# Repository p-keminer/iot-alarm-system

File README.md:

<div align="center">

</div>

---

<div align="center">
  
  &nbsp;&nbsp;&nbsp;&nbsp;&nbsp;&nbsp;
  
  &nbsp;&nbsp;&nbsp;&nbsp;&nbsp;&nbsp;
 
</div>

---

# IoT-Alarmanlage

Die IoT-Alarmanlage basiert auf einem `Elegoo Uno R3`, zwei `ESP8266` und einem `Raspberry Pi Zero 2 W`. RFID und zwei Reed-Sensoren steuern die lokale Alarm-FSM. Ein Funkpfad uebertraegt Alarmzustaende an den Empfaenger; das Dashboard zeigt Telemetrie, Logs und Aufnahmen und sendet freigegebene Befehle.

Dieses Projekt entstand in meinem ersten Studiensemester und war mein erstes Lernprojekt.

```text
RFID + 2x Reed -> Uno-FSM -> UART -> ESP-Sender -> HMAC-UDP -> ESP-Empfaenger
                         |
                         +-> USB-Serial <-> Alarm-Monitor <-> lokale IPC <-> Dashboard

ESP-Sender + ESP-Empfaenger <-> HTTP/JSON im isolierten IoT-WLAN <-> Raspberry Pi / PHP-API
```

## Aktueller Stand

| Ziel | Aktiver Sketch |
|---|---|
| Uno R3 | `firmware/elegoo_uno_r3/sketchR3/alarm_system/alarm_system.ino` |
| ESP-Sender | `firmware/esp8266/sender/sender.ino` |
| ESP-Empfaenger | `firmware/esp8266/receiver/receiver.ino` |

- Der Uno akzeptiert ohne private `uid_whitelist.local.h` keine Karte. Scharf-/Alarmzustand liegt CRC-geschuetzt in zwei EEPROM-Slots; ein offener Reed-Kreis loest scharf Alarm aus.
- UDP nutzt HMAC-SHA256, strikt monotone persistente Sequenzen und signierte ACKs. HTTP-Zustellungen nutzen getrennte Geraete-Token/-HMACs und ein durables `ALARMv2`-Apply-Journal.
- `nginx`/`PHP-FPM` bedienen den Browser per HTTPS und die ESPs ueber einen auf das IoT-WLAN beschraenkten HTTP-Endpunkt. Der Dienst `iot-alarm-monitor` besitzt exklusiv Serial, Recorder und deren Loeschpfade.
- Der Prototyp besitzt keine formale Produkt-, Safety- oder Security-Freigabe.

## Repository

| Pfad | Inhalt |
|---|---|
| `firmware/` | drei aktive Arduino-Ziele |
| `web/` | Dashboard, API, Monitor und Deploy-Vorlagen |
| `hardware/` | KiCad-, Gerber- und Aufbauquellen |
| `mechanics/` | STL-Dateien und Vorschauen |
| `media/` | Projektfotos und fuenf Demo-GIFs |
| `docs/`, `tests/` | kanonische Dokumentation und Nachweise |

## Einstieg

[Build](docs/BUILD.md#deutsch) · [Hardware](docs/HARDWARE.md#deutsch) · [Web-Dashboard](web/README.md#deutsch) · [Tests](docs/TESTING.md#deutsch) · [Safety](SAFETY.md#deutsch) · [Security](SECURITY.md#deutsch)

## Sicherheitsgrenze

Das System ist ein nicht zertifizierter Lernprototyp. Ausfaelle von Strom, Funk, Speicher, Kamera oder Hardware koennen seine Funktion beeintraechtigen.

## Lokale Konfiguration

RFID-UIDs, WLAN-Daten, Token, HMAC-Secrets, Passwoerter, PINs und Laufzeitdaten bleiben lokal. Vorlagen enden auf `.example`; private Werte liegen in ignorierten `*.local.*`-Dateien oder im geschuetzten `web/data/`.

## Lizenz

Projekt-eigene Inhalte stehen unter der [MIT-Lizenz](LICENSE.md); Drittmaterial behaelt seine jeweiligen Rechte.

<div align="center">

</div>

---

# IoT Alarm System

The IoT alarm system uses an `Elegoo Uno R3`, two `ESP8266` nodes, and a `Raspberry Pi Zero 2 W`. RFID and two reed sensors drive the local alarm FSM. A radio link sends alarm states to the receiver; the dashboard displays telemetry, logs, and recordings and sends approved commands.

This project began during the first semester of my degree and was my first learning project.

```text
RFID + 2x reed -> Uno FSM -> UART -> ESP sender -> HMAC UDP -> ESP receiver
                           |
                           +-> USB serial <-> alarm monitor <-> local IPC <-> dashboard

ESP sender + ESP receiver <-> HTTP/JSON on the isolated IoT WiFi <-> Raspberry Pi / PHP API
```

## Current Status

| Target | Active sketch |
|---|---|
| Uno R3 | `firmware/elegoo_uno_r3/sketchR3/alarm_system/alarm_system.ino` |
| ESP sender | `firmware/esp8266/sender/sender.ino` |
| ESP receiver | `firmware/esp8266/receiver/receiver.ino` |

- Without private `uid_whitelist.local.h`, the Uno accepts no card. Armed/alarm state is CRC-protected across two EEPROM slots; either open reed circuit triggers an armed system.
- UDP uses HMAC-SHA256, strict monotonic persistent sequences, and signed ACKs. HTTP delivery uses separate device tokens/HMACs and a durable `ALARMv2` apply journal.
- `nginx`/`PHP-FPM` serve the browser over HTTPS and the ESPs through an HTTP endpoint restricted to the IoT WiFi. The `iot-alarm-monitor` service exclusively owns serial, the recorder, and their deletion paths.
- The prototype has no formal product, safety, or security approval.

## Repository

| Path | Contents |
|---|---|
| `firmware/` | three active Arduino targets |
| `web/` | dashboard, API, monitor, and deployment templates |
| `hardware/` | KiCad, Gerber, and assembly sources |
| `mechanics/` | STL files and previews |
| `media/` | project photos and five demo GIFs |
| `docs/`, `tests/` | canonical documentation and evidence |

## Getting Started

[Build](docs/BUILD.md#english) · [Hardware](docs/HARDWARE.md#english) · [Web dashboard](web/README.md#english) · [Tests](docs/TESTING.md#english) · [Safety](SAFETY.md#english) · [Security](SECURITY.md#english)

## Security Boundary

The system is an uncertified learning prototype. Power, radio, storage, camera, or hardware failures may impair its operation.

## Local Configuration

RFID UIDs, WiFi credentials, tokens, HMAC secrets, passwords, PINs, and runtime data remain local. Templates end in `.example`; private values live in ignored `*.local.*` files or protected `web/data/`.

## License

Project-owned content uses the [MIT License](LICENSE.md); third-party material retains its respective rights.

<div align="center">

</div>

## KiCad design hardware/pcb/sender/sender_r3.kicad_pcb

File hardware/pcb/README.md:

## PCB – Versorgungsvarianten (ESP + Elegoo Uno R3)

In diesem Verzeichnis befinden sich **zwei PCB-Varianten** für das **sender** System, die sich ausschließlich in der Art der Stromversorgung unterscheiden.

---

## Überblick über die Varianten

### Versorgung über Elegoo Uno R3 (Basisversion)

Diese Version versorgt den ESP **direkt über den Elegoo Uno R3**.

- Ausgelegt für:
  - Grundlogik
  - geringe bis moderate WLAN-Aktivität
- Einschränkungen:
  - begrenzte Stromreserve
  - nicht optimal für hohe WLAN-Lasten oder OTA-Updates

**HINWEIS:** NICHT empfohlen, falls Elegoo Uno R3 über USB per Pi versorgt    werden soll.

---

### Externe Stromversorgung (Erweiterte Version)

Diese Version benötigt eine **separate externe Spannungsversorgung** für den ESP.

- Ausgelegt für:
  - hohe Stromspitzen beim WLAN-Senden und -Empfangen
  - OTA-Updates
  - stabile Funkverbindungen unter Last
- Vorteile:
  - deutlich stabilere Spannungsversorgung
  - minimiertes Risiko von Resets oder Verbindungsabbrüchen
  - bessere Skalierbarkeit für Erweiterungen

**Vorgesehen für erweiterte und leistungsintensivere Systeme**

---

### Technischer Hintergrund

Beim ESP treten insbesondere während **WLAN-Übertragungen und OTA-Vorgängen** kurzzeitig hohe Stromspitzen auf.  
Die externe Versorgungsvariante berücksichtigt diese Lastfälle gezielt, während die direkte Versorgung über den Elegoo Uno R3 für die **reine Grundfunktionalität ausreichend ist**.

---

### Empfehlung

- **Prototypen / Basislogik:** Versorgung über Elegoo Uno R3  
- **Erweiterte oder produktionsnahe Systeme:** externe Stromversorgung

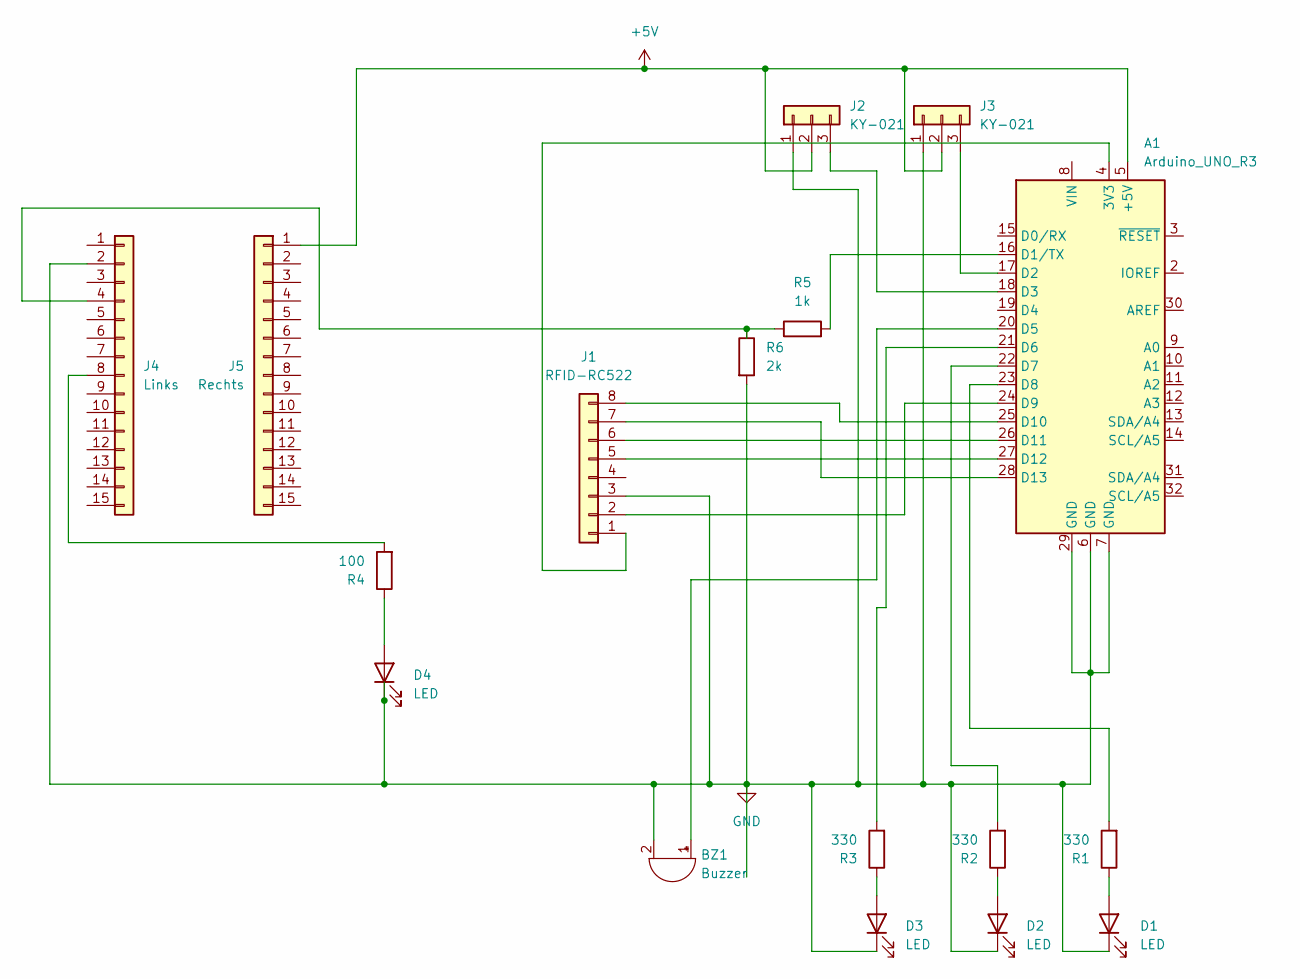
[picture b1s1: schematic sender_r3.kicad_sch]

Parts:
A1: Arduino_UNO_R3
BZ1: Buzzer; Buzzer_D14mm_H7mm_P10mm
D1, D2, D3, D4: LED; LED_D5.0mm
J1: RFID-RC522; PinHeader_1x08_P2.54mm_Vertical
J2, J3: KY-021; PinHeader_1x03_P2.54mm_Vertical
J4: Links; PinHeader_1x15_P2.54mm_Vertical
J5: Rechts; PinHeader_1x15_P2.54mm_Vertical
R1, R2, R3: 330; R_Axial_DIN0207_L6.3mm_D2.5mm_P7.62mm_Horizontal
R4: 100; R_Axial_DIN0207_L6.3mm_D2.5mm_P7.62mm_Horizontal
R5: 1k; R_Axial_DIN0207_L6.3mm_D2.5mm_P7.62mm_Horizontal
R6: 2k; R_Axial_DIN0207_L6.3mm_D2.5mm_P7.62mm_Horizontal

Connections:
+5V: A1.5 (+5V), J2.2, J3.2, J5.1
GND: A1.6 (GND), A1.7 (GND), A1.29 (GND), BZ1.2 (-), D1.1 (K), D2.1 (K), D3.1 (K), D4.1 (K), J1.3, J2.1, J3.1, J4.2, R6.2
unnamed: A1.4 (3V3), J1.1
unnamed: A1.16 (D1/TX), R5.2
unnamed: A1.17 (D2), J3.3
unnamed: A1.18 (D3), J2.3
unnamed: A1.20 (D5), BZ1.1 (+)
unnamed: A1.21 (D6), R3.2
unnamed: A1.22 (D7), R2.2
unnamed: A1.23 (D8), R1.2
unnamed: A1.24 (D9), J1.2
unnamed: A1.25 (D10), J1.8
unnamed: A1.26 (D11), J1.6
unnamed: A1.27 (D12), J1.5
unnamed: A1.28 (D13), J1.7
unnamed: D1.2 (A), R1.1
unnamed: D2.2 (A), R2.1
unnamed: D3.2 (A), R3.1
unnamed: D4.2 (A), R4.1
unnamed: J4.4, R5.1, R6.1
unnamed: J4.8, R4.2

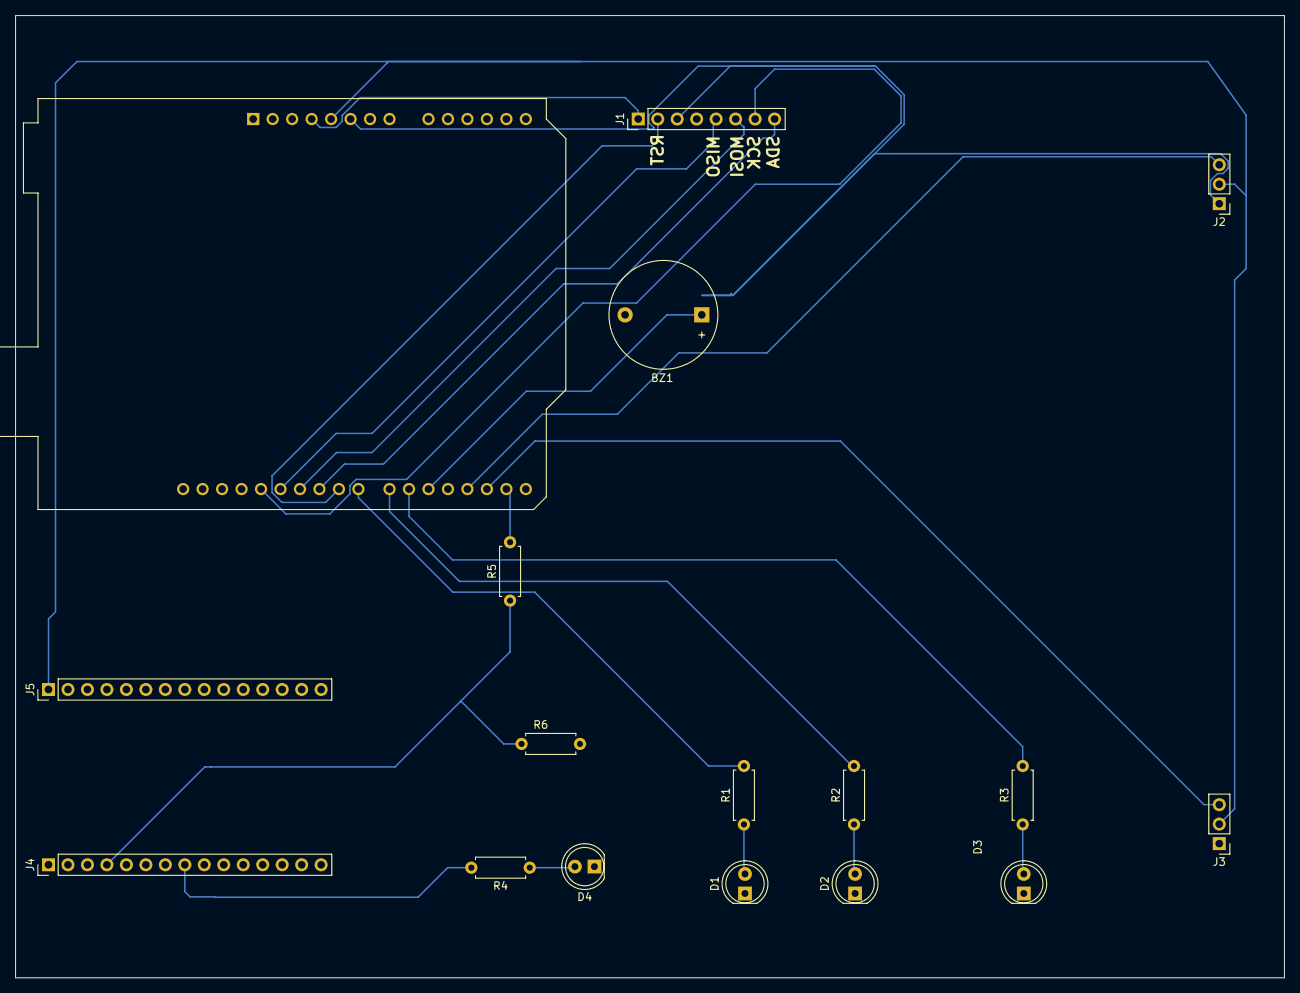
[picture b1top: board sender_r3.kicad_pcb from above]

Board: 2 copper layers, 165.5 x 125.5 mm, 17 parts (0 on the bottom side), 21 nets.

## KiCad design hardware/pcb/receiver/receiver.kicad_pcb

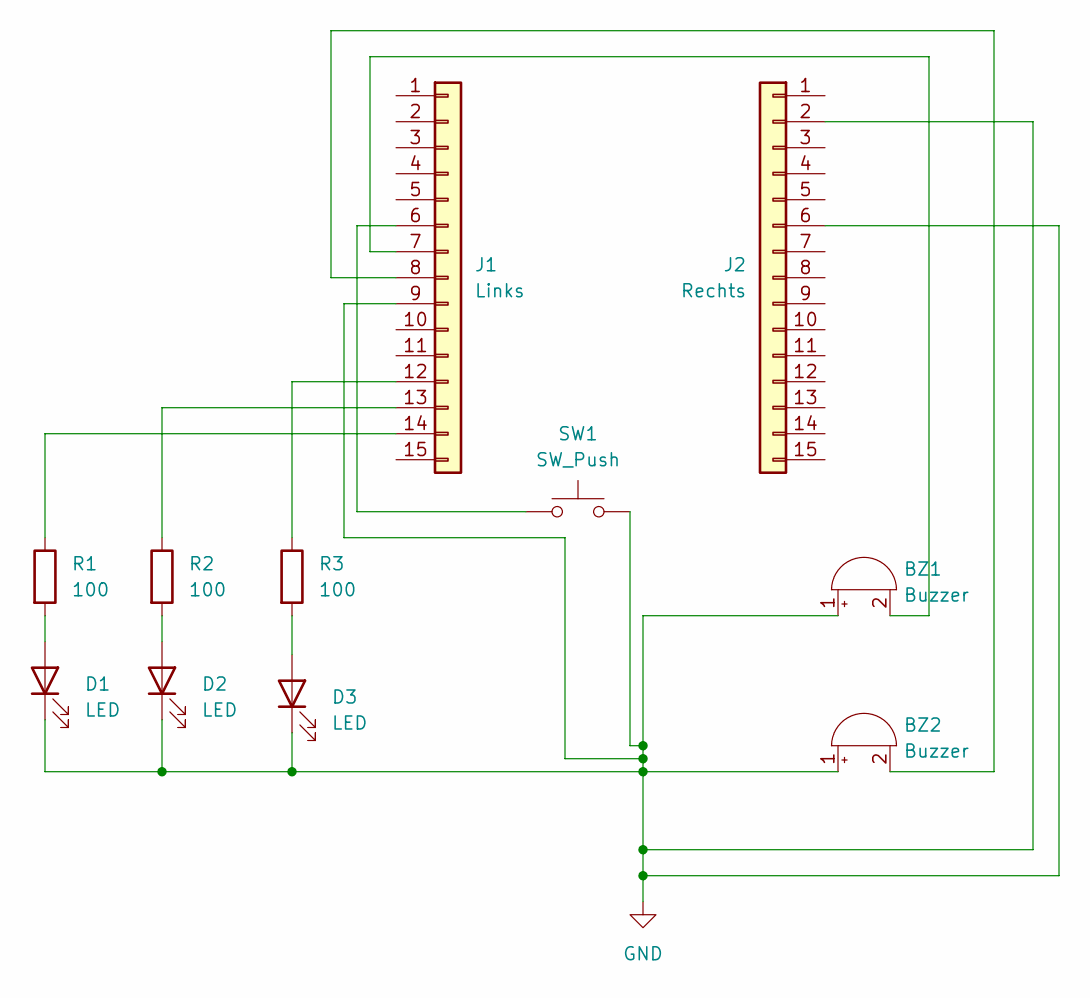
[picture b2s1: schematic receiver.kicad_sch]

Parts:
BZ1, BZ2: Buzzer; Buzzer_D14mm_H7mm_P10mm
D1, D2, D3: LED; LED_D5.0mm
J1: Links; PinSocket_1x15_P2.54mm_Vertical
J2: Rechts; PinSocket_1x15_P2.54mm_Vertical
R1, R2, R3: 100; R_Axial_DIN0207_L6.3mm_D2.5mm_P7.62mm_Horizontal
SW1: SW_Push; SW_PUSH_1P1T_6x3.5mm_H5.0_APEM_MJTP1250

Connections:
GND: BZ1.1 (+), BZ2.1 (+), D1.1 (K), D2.1 (K), D3.1 (K), J1.9, J2.2, J2.6, SW1.2
unnamed: BZ1.2 (-), J1.7
unnamed: BZ2.2 (-), J1.8
unnamed: D1.2 (A), R1.2
unnamed: D2.2 (A), R2.2
unnamed: D3.2 (A), R3.2
unnamed: J1.6, SW1.1
unnamed: J1.12, R3.1
unnamed: J1.13, R2.1
unnamed: J1.14, R1.1

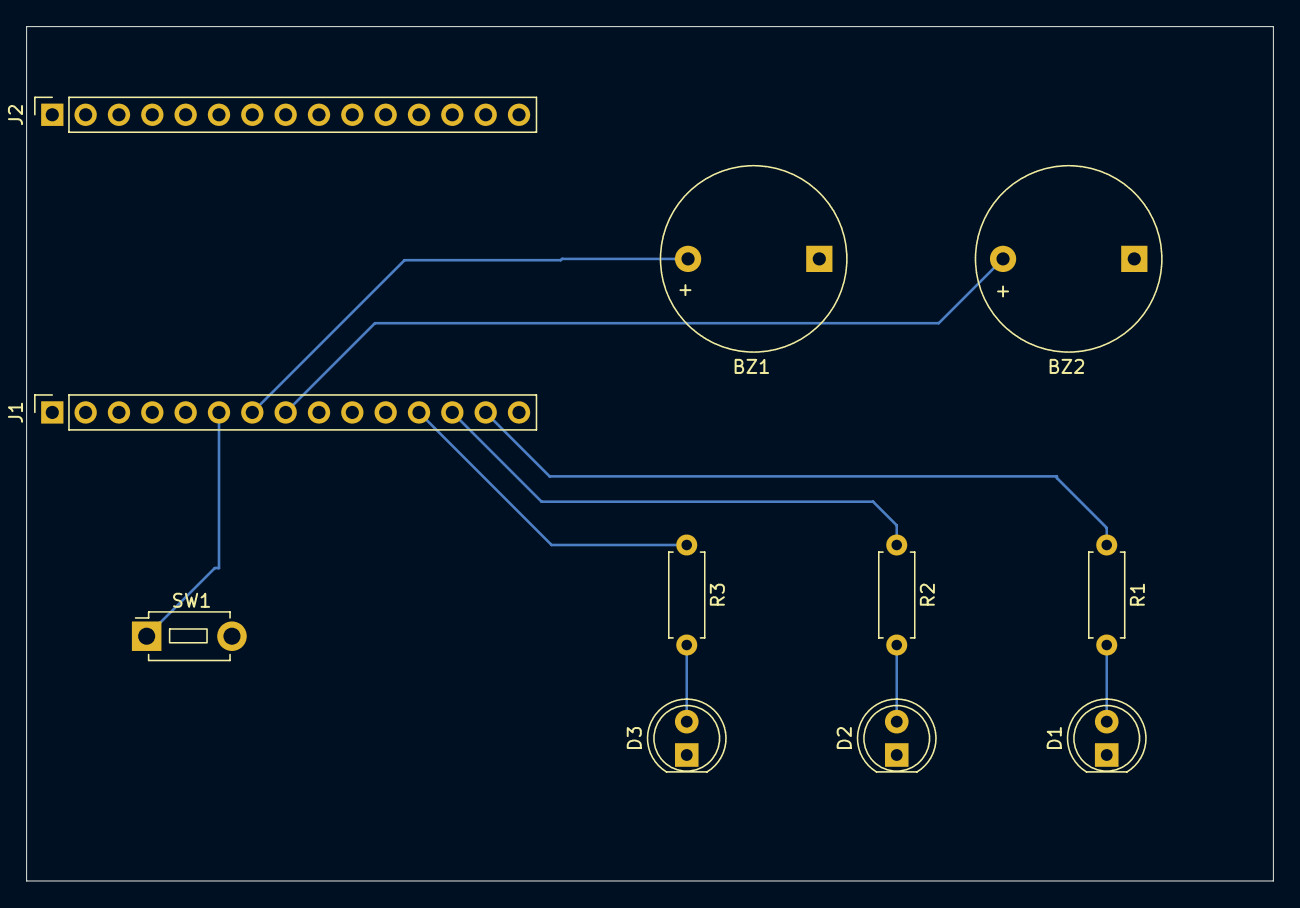
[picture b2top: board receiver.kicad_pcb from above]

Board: 2 copper layers, 95.0 x 65.1 mm, 11 parts (0 on the bottom side), 10 nets.

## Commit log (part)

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2026-01-08 Rename lessonslearned.txt to lessonsLearned.txt
2026-01-08 Rename LICENSE.md to LICENSE
2026-01-08 Rename LICENSE to LICENSE.md
2026-01-15 mDNS, BackUpWLAN & IP Prüfung hinzugefügt
2026-01-16 ACK, mDNS & BackUpWLAN hinzugefügt
2026-01-21 Badges bearbeitet
2026-01-21 Masseflächen ergänzt
2026-01-21 lessonsLearned Badge ergänzt
2026-01-21 PCB mit externer Stromversorgung ergänzt
2026-01-21 README für PCBs ergänzt
2026-01-21 README.md ergänzt
2026-01-21 pinmapping ElegooUnoR3.md erstellt
2026-01-21 pinmapping EmpängerEsp.md erstellt
2026-01-21 pinmapping SenderEsp.md erstellt
2026-01-21 Badges überarbeitet in README.md (vorläufige Version)
2026-01-22 Badges Strukturiert, visuell README.md überarbeitet
2026-01-23 docs: gitignore hinzugefuegt
2026-01-23 Inhalt geändert in .gitignore
2026-01-25 ordnerstruktur aktualisiert
2026-01-25 PCBs hinzugefügt
2026-01-25 README.md aktualisiert, gifs&videos hinzugefuegt, strukturiert
2026-01-25 gifs ueberarbeitet
2026-01-25 layout gifs final
2026-01-25 Deleted directory
2026-01-25 pinmapping überarbeitet
2026-01-29 OTA, Token-Auth, Telnet(Brute Force), Wm, Structs etc. hinzugefuegt
2026-01-29 Gehaeuse fuer PCB_Empfaenger hinzugefuegt
2026-01-29 LessonsLearned ergaenzt, Readme überarbeitet
2026-01-29 Badges erweitert
2026-01-29 lessosnLearned ueberarbeitet
2026-01-29 neue .stl Datei hinzugefuegt
2026-01-29 Pfade überarbeitet, Badges angepasst
2026-01-29 leerzeichen hinzugefügt
2026-02-08 Low Level Crypto, Easter Eggs, Api anbindung hinzugefügt
2026-02-08 Grundgerüst Webserver hinzugefügt
2026-02-08 Readme und LessonsLearned an Webserver angepasst
2026-02-08 Badge aktualisiert
2026-02-08 Badge funktioniert
2026-02-08 Tools überarbeitet
2026-02-09 .mds überarbeitet und insg. auf den neuesten Stand gebracht
2026-02-09 mainREADME.md neuester stand
2026-02-09 Workflow Diagramm überarbeitet
2026-02-09 Screenshots Webserver hinzugefügt
2026-02-09 Screenshots sortiert
2026-02-09 Firmware upgrade
2026-02-09 Refactor: HAL-Architektur, State Machine und Hardware-Watchdog
2026-02-09 Readme überarbeitet
2026-02-09 firmware update
2026-02-11 Refactoring Node-Sketches HAL/FSM
2026-02-11 Webserver Security hardened & Big bugs fixed
2026-02-11 Webserver Migration & Refactoring hinzugefügt
2026-02-11 READMEs überarbeitet v1
2026-02-11 READMEs überarbeitet v2
2026-02-11 Navigation & Badges überarbeitet
2026-02-11 Navigation & Badges überarbeitet v3
2026-02-11 Navigation & Badges überarbeitet v4
2026-02-11 Navigation & Badges überarbeitet v5
2026-02-12 Sever stabilisiert und finalisiert
2026-02-12 3d_prints vollständig
2026-02-12 Tools erweitert & strukturiert
2026-02-12 Sanitize default credentials and inmprove documentation for public release
2026-02-12 Sanitize documentation, screenshots and default configuration for public release
2026-02-12 Normalize project structure and fully repair documentation and media links
2026-02-12 refactor: normalize filenames and directories to english snake_case
2026-02-12 fix: update README links after file renaming
2026-02-12 Add gitleaks secret scan workflow
2026-02-12 Fix gitleaks action config
2026-02-12 Add security configs and tooling
2026-02-12 Rename .pre-commit-config.yaml to .pre-commit-config.yml
2026-02-13 Refactor: organized files & first semester final push
2026-02-13 renamed data
2026-02-13 1semster final commit (commented files)
2026-02-23 docs: Kurzbeschreibungen und Übersicht überarbeitet
    - Main README: Kurzbeschreibung erweitert um HMAC-SHA256, Resilienz-Features und Remote-Management
    - Main README: Übersicht/Overview zu durchgängig lesbarem Fließtext umgeschrieben (DE + EN)
    - Sender README: Tagline ergänzt um UDP-Broadcast-Fallback, WiFi-Failback, Remote-Management
    - Receiver README: Tagline ergänzt um Flash Wear-Leveling und Remote-Override
    - Elegoo Uno R3 README: Kurzbeschreibung um Redundanz-Logik, HAL/FSM und Hardware-Watchdog erweitert
    https://claude.ai/code/session_015kVxnK9r7EuaRt6bCSX6PX
2026-02-23 docs: Sicherheitsfeatures und Sketch-Header aktualisiert
    - Main README Receiver: Binary String Obfuscation, Remote Override, Flash Wear-Leveling,
    Emergency QoS ergänzt; Telnet-Brute-Force-Schutz entfernt
    - Main README Sender: Eigene Security-Sektion ergänzt, UDP-Broadcast-Fallback,
    Active WiFi-Failback, Remote-Config/Wipe, Software-Watchdog, Audit Trail hinzugefügt;
    OTA/Telnet-Eintrag entfernt; sketch_receiver Tippfehler im Sender-Abschnitt korrigiert
    - sketch_receiver.ino: Header auf V14.0 aktualisiert, Resilienz-Block ergänzt,
2026-02-23 docs: Kommunikationsarten einheitlich aktualisiert und neue Sektion ergänzt
    - Inhaltsverzeichnis: Eintrag für Kommunikationsarten/Communication Protocols ergänzt
    - Kurzbeschreibung (DE + EN): UART, UDP und HTTP/JSON API konsistent erwähnt
    - Übersicht (DE + EN): Kommunikationswege vollständig beschrieben (UART, UDP, HTTP/JSON API)
    - Features-Liste: Kommunikationszeile auf UART, UDP unicast/broadcast, HTTP/JSON API, mDNS erweitert
    - Neue Sektion Kommunikationsarten mit Tabelle aller Protokolle, Strecken und Zwecke eingefügt
    https://claude.ai/code/session_015kVxnK9r7EuaRt6bCSX6PX
2026-02-23 docs: VPN aus Schwachstellenanalyse entfernt, Badge ergänzt
    - firmware/esp8266/README.md: VPN-Anforderung aus Netzwerk-Filterung entfernt,
    Layer-3 Flooding-Schutz bleibt als externe Router-Leistung bestehen
    - README.md: Badge für Schwachstellenanalyse (rot) in Badge-Zeile eingefügt
    https://claude.ai/code/session_015kVxnK9r7EuaRt6bCSX6PX
2026-02-23 Refactorized 23.02.2026
2026-02-23 Refactor index.php into modular file structure
    Split the monolithic 2741-line index.php into separate, focused files:
    PHP includes:
    - includes/config.php – Settings loading & brute-force configuration
    - includes/auth.php – Session management, timeout, logout, BF functions
    - includes/data.php – Telemetry & diagnostic data loading
    Views:
